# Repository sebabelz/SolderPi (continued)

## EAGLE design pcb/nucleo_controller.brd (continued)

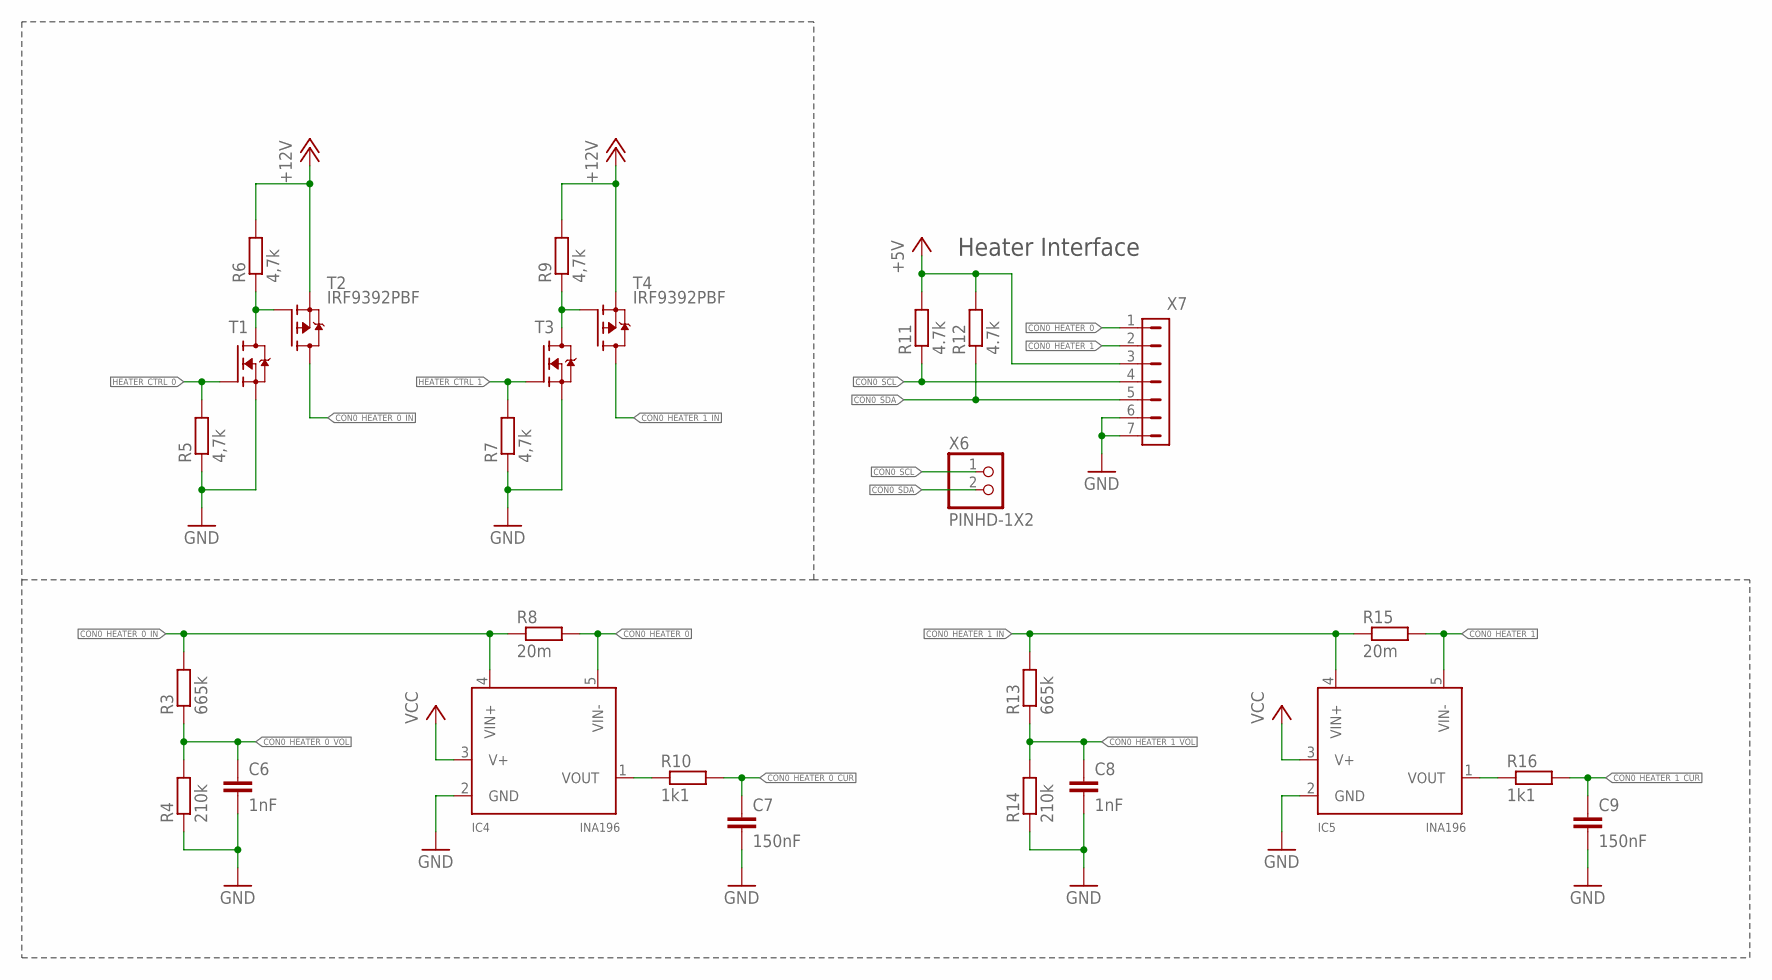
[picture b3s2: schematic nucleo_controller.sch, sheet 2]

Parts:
C6, C8: 1nF; C0603
C7, C9: 150nF; C0603
IC4, IC5: INA196; SOT23-5L
R3, R13: 665k; R0603
R4, R14: 210k; R0603
R5, R6, R7, R9: 4,7k; R0805
R8, R15: 20m; R1206
R10, R16: 1k1; R0603
R11, R12: 4.7k; R0603
T1, T3: NVR4003NT3G; SOT23
T2, T4: IRF9392PBF; SO8
X6: PINHD-1X2; 1X02
X7: NANOFIT-7

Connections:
+5V: R11.2, R12.2, X7.3; also elsewhere on the board
+12V: R6.2, R9.2, T2.1 (S), T2.2 (S), T2.3 (S), T4.1 (S), T4.2 (S), T4.3 (S); also elsewhere on the board
CON0_HEATER_0: IC4.5 (VIN-), R8.2, X7.1
CON0_HEATER_0_CUR: C7.1, R10.2; also elsewhere on the board
CON0_HEATER_0_IN: IC4.4 (VIN+), R3.2, R8.1, T2.5 (D), T2.6 (D), T2.7 (D), T2.8 (D)
CON0_HEATER_0_VOL: C6.1, R3.1, R4.2; also elsewhere on the board
CON0_HEATER_1: IC5.5 (VIN-), R15.2, X7.2
CON0_HEATER_1_CUR: C9.1, R16.2; also elsewhere on the board
CON0_HEATER_1_IN: IC5.4 (VIN+), R13.2, R15.1, T4.5 (D), T4.6 (D), T4.7 (D), T4.8 (D)
CON0_HEATER_1_VOL: C8.1, R13.1, R14.2; also elsewhere on the board
CON0_SCL: R11.1, X6.1, X7.4; also elsewhere on the board
CON0_SDA: R12.1, X6.2, X7.5; also elsewhere on the board
GND: C6.2, C7.2, C8.2, C9.2, IC4.2 (GND), IC5.2 (GND), R4.1, R5.1, R7.1, R14.1, T1.2 (S), T3.2 (S), X7.6, X7.7; also elsewhere on the board
HEATER0_AD_OUT0: IC4.1 (VOUT), R10.1
HEATER0_AD_OUT1: IC5.1 (VOUT), R16.1
HEATER0_G0: R6.1, T1.3 (D), T2.4 (G)
HEATER0_G1: R9.1, T3.3 (D), T4.4 (G)
HEATER_CTRL_0: R5.2, T1.1 (G); also elsewhere on the board
HEATER_CTRL_1: R7.2, T3.1 (G); also elsewhere on the board
VCC: IC4.3 (V+), IC5.3 (V+); also elsewhere on the board

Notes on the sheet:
Heater Interface

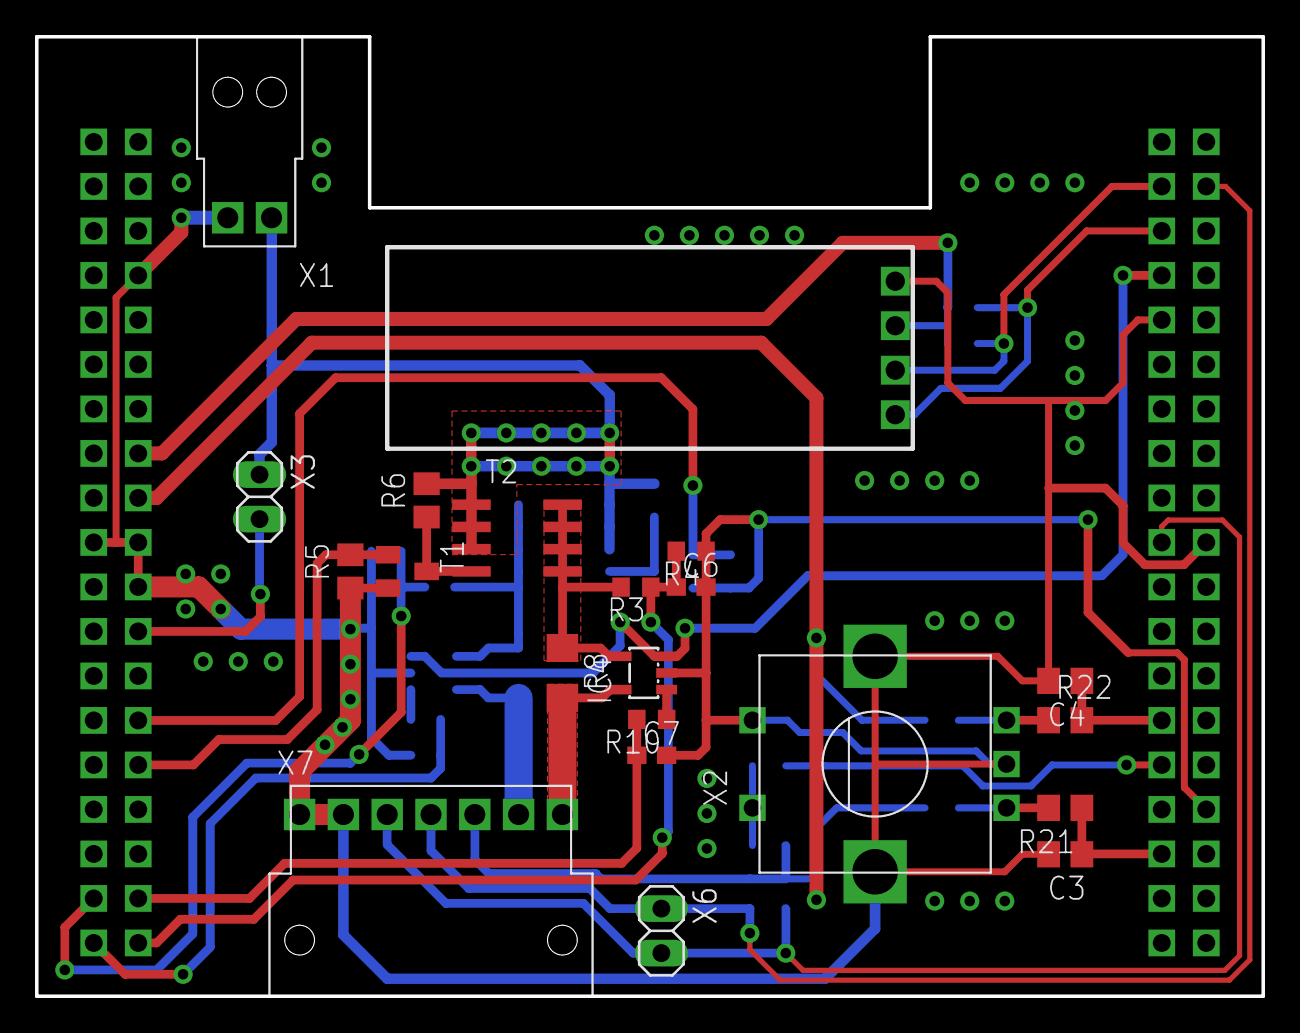
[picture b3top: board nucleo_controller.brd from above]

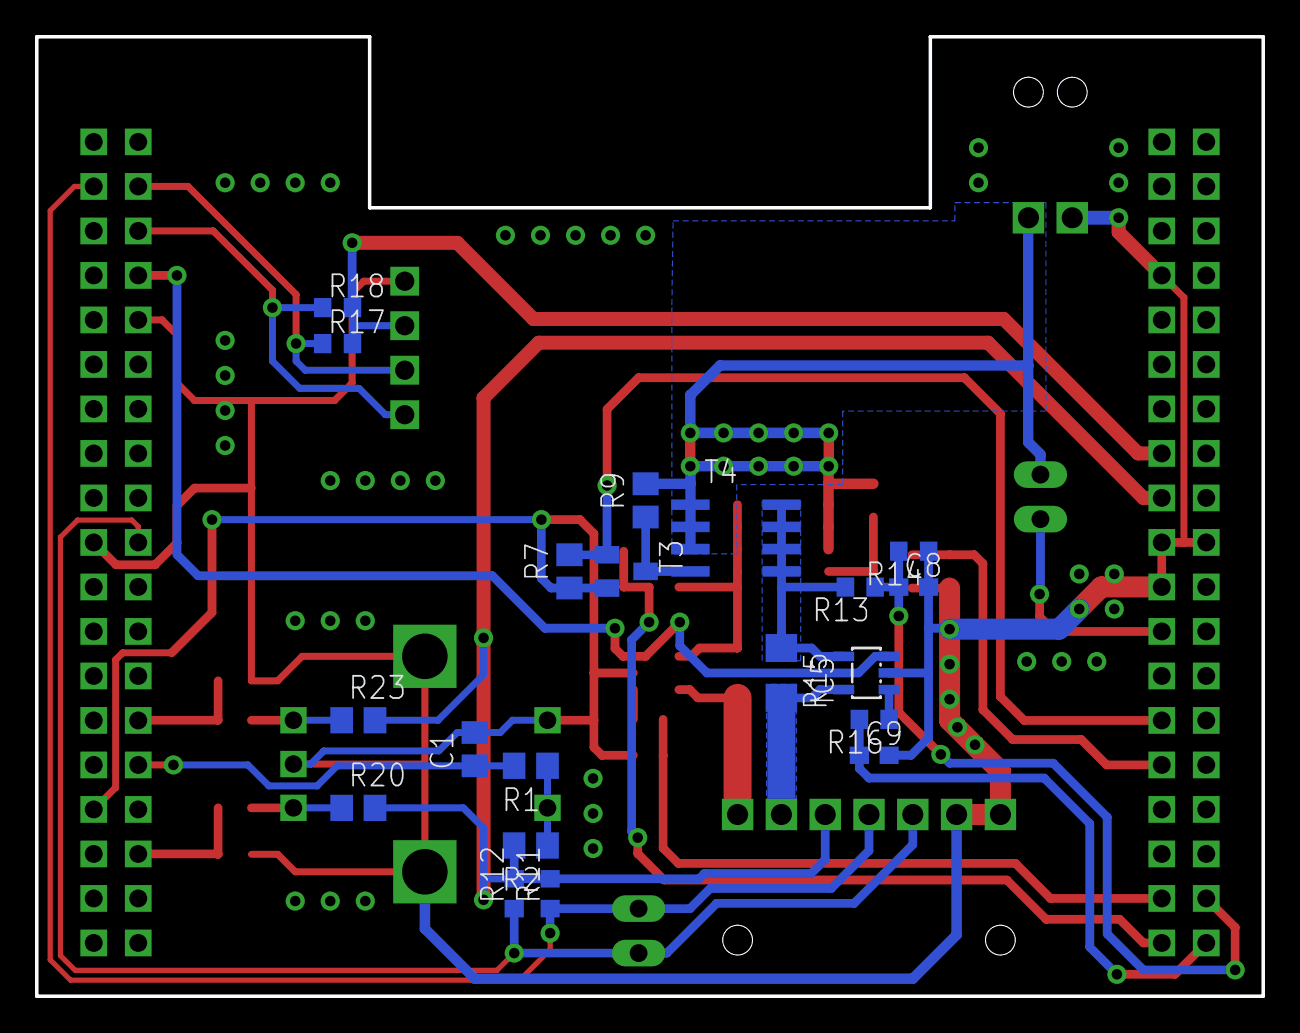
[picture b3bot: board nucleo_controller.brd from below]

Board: 2 copper layers, 70.0 x 54.8 mm, 42 parts (20 on the bottom side), 30 nets.

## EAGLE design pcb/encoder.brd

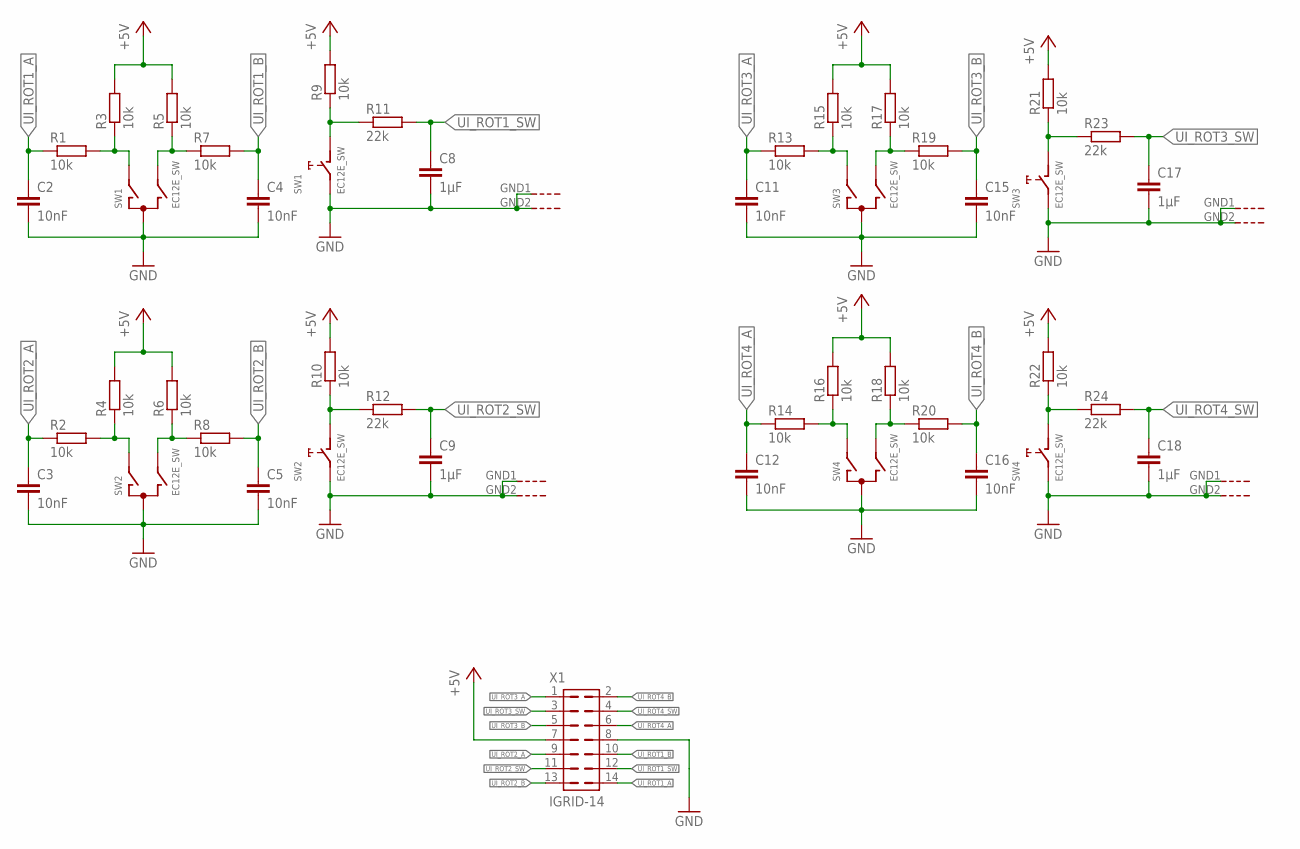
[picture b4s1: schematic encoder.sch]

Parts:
C2, C3, C4, C5, C11, C12, C15, C16: 10nF; C0805
C8, C9, C17, C18: 1µF; C0805
R1, R2, R3, R4, R5, R6, R7, R8, R9, R10, R13, R14, R15, R16, R17, R18, R19, R20, R21, R22: 10k; R0805
R11, R12, R23, R24: 22k; R0805
SW1, SW2, SW3, SW4: EC12E_SW; ALPS_EC12E_SW
X1: IGRID-14; I-GRID-14

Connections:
+5V: R3.2, R4.2, R5.2, R6.2, R9.2, R10.2, R15.2, R16.2, R17.2, R18.2, R21.2, R22.2, X1.7
GND: C2.2, C3.2, C4.2, C5.2, C8.2, C9.2, C11.2, C12.2, C15.2, C16.2, C17.2, C18.2, SW1.C, SW1.E (2), SW1.GND1 (G), SW1.GND2 (G), SW2.C, SW2.E (2), SW2.GND1 (G), SW2.GND2 (G), SW3.C, SW3.E (2), SW3.GND1 (G), SW3.GND2 (G), SW4.C, SW4.E (2), SW4.GND1 (G), SW4.GND2 (G), X1.8
UI_ROT1_A: C2.1, R1.1, X1.14
UI_ROT1_A_UNFIL: R1.2, R3.1, SW1.A
UI_ROT1_B: C4.1, R7.2, X1.10
UI_ROT1_B_UNFIL: R5.1, R7.1, SW1.B
UI_ROT1_SW: C8.1, R11.2, X1.12
UI_ROT1_SW_R: R9.1, R11.1, SW1.D (1)
UI_ROT2_A: C3.1, R2.1, X1.9
UI_ROT2_A_UNFIL: R2.2, R4.1, SW2.A
UI_ROT2_B: C5.1, R8.2, X1.13
UI_ROT2_B_UNFIL: R6.1, R8.1, SW2.B
UI_ROT2_SW: C9.1, R12.2, X1.11
UI_ROT2_SW_R: R10.1, R12.1, SW2.D (1)
UI_ROT3_A: C11.1, R13.1, X1.1
UI_ROT3_A_UNFIL: R13.2, R15.1, SW3.A
UI_ROT3_B: C15.1, R19.2, X1.5
UI_ROT3_B_UNFIL: R17.1, R19.1, SW3.B
UI_ROT3_SW: C17.1, R23.2, X1.3
UI_ROT3_SW_R: R21.1, R23.1, SW3.D (1)
UI_ROT4_A: C12.1, R14.1, X1.6
UI_ROT4_A_UNFIL: R14.2, R16.1, SW4.A
UI_ROT4_B: C16.1, R20.2, X1.2
UI_ROT4_B_UNFIL: R18.1, R20.1, SW4.B
UI_ROT4_SW: C18.1, R24.2, X1.4
UI_ROT4_SW_R: R22.1, R24.1, SW4.D (1)

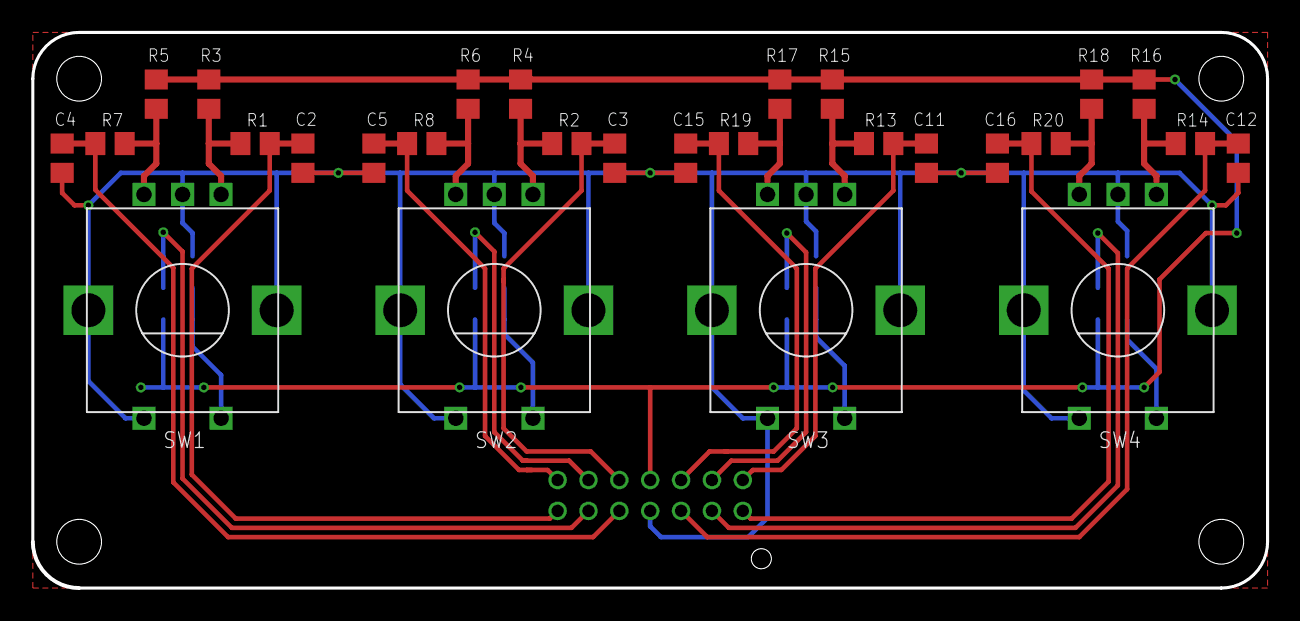
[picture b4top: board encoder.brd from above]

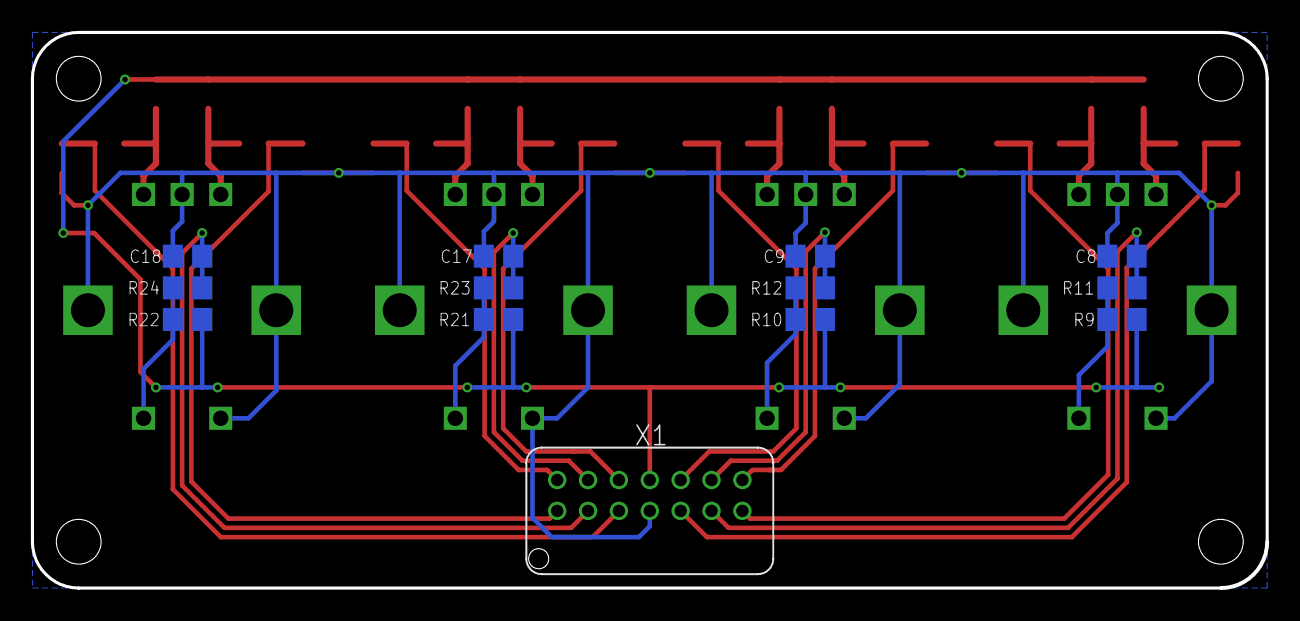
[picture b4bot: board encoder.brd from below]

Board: 2 copper layers, 80.0 x 36.0 mm, 41 parts (13 on the bottom side), 26 nets.

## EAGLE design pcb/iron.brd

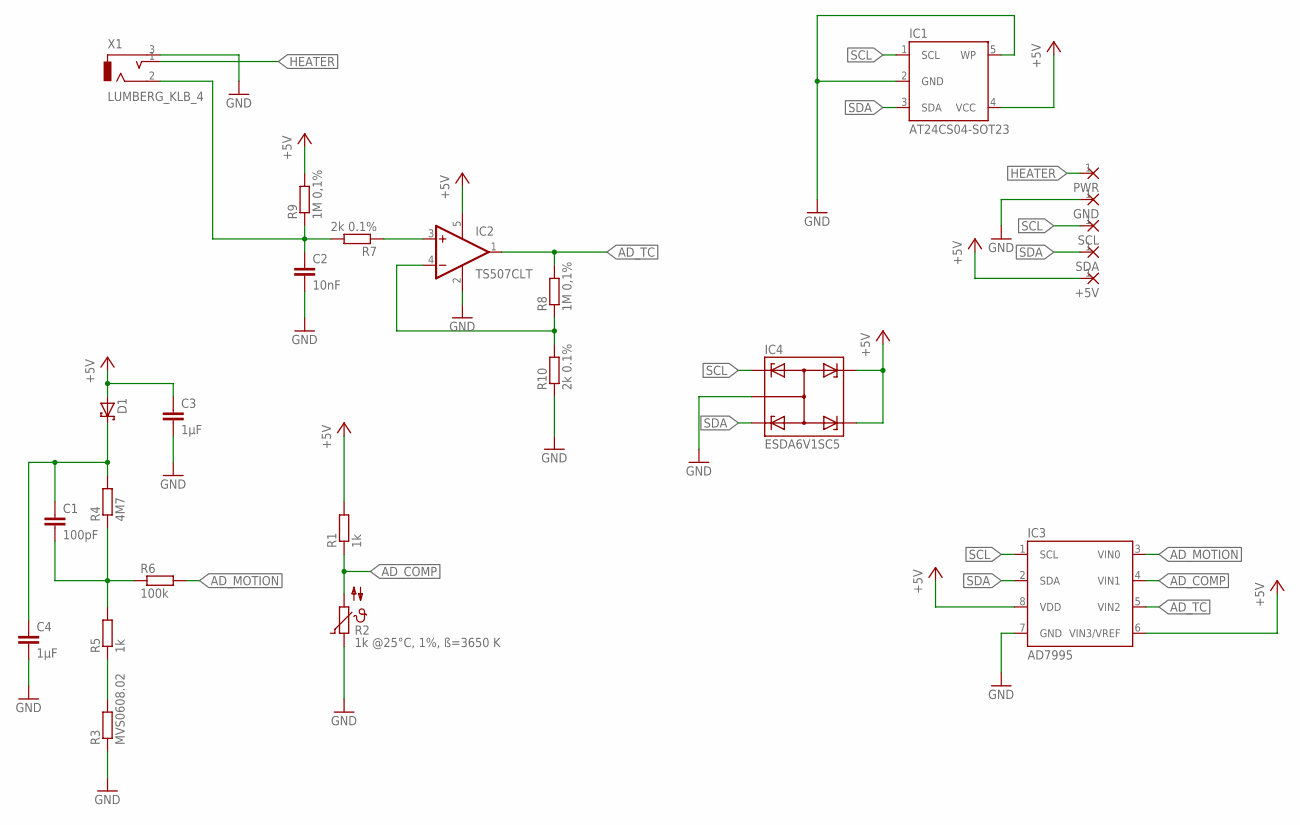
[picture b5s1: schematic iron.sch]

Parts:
+5V: 1,6/0,8
C1: 100pF; C0603
C2: 10nF; C0603
C3, C4: 1µF; C0603
D1: BAT54H; SOD123-F
GND: 1,6/0,8
IC1: AT24CS04-SOT23; SOT23-5L
IC2: TS507CLT; SOT23-5L
IC3: AD7995; SOT23-8
IC4: ESDA6V1SC5; SOT23-5L
PWR: 1,6/0,8
R1, R5: 1k; R0603
R2: 1k @25°C, 1%, ß=3650 K; R0603
R3: MVS0608.02; VIBRA-SNS
R4: 4M7; R0603
R6: 100k; R0603
R7, R10: 2k 0.1%; R0603
R8, R9: 1M 0,1%; R0603
SCL: 1,6/0,8
SDA: 1,6/0,8
X1: LUMBERG_KLB_4; 3.5_MM_AUDIO_JACK

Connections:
+5V: +5V.1, C3.1, D1.2 (A), IC1.4 (VCC), IC2.5 (V+), IC3.6 (VIN3/VREF), IC3.8 (VDD), IC4.4, IC4.5, R1.2, R9.2
AD_COMP: IC3.4 (VIN1), R1.1, R2.2
AD_MOTION: IC3.3 (VIN0), R6.2
AD_TC: IC2.1 (OUT), IC3.5 (VIN2), R8.2
FEEDBACK: IC2.4 (-IN), R8.1, R10.2
GND: C2.2, C3.2, C4.2, GND.1, IC1.2 (GND), IC1.5 (WP), IC2.2 (V-), IC3.7 (GND), IC4.2, R2.1, R3.P$1 (1), R10.1, X1.3
HEATER: PWR.1, X1.1
MOTION_DIV: R3.P$2 (2), R5.1
MOTION_FIL: C1.2, R4.1, R5.2, R6.1
unnamed: C1.1, C4.1, D1.1 (C), R4.2
SCL: IC1.1 (SCL), IC3.1 (SCL), IC4.1, SCL.1
SDA: IC1.3 (SDA), IC3.2 (SDA), IC4.3, SDA.1
THERMO_FIL: IC2.3 (+IN), R7.1
THERMO_UNFIL: C2.1, R7.2, R9.1, X1.2

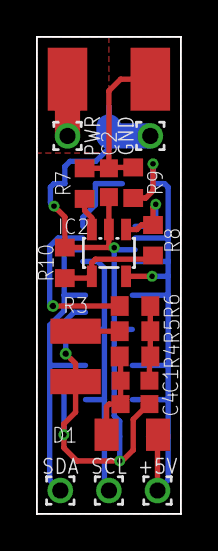
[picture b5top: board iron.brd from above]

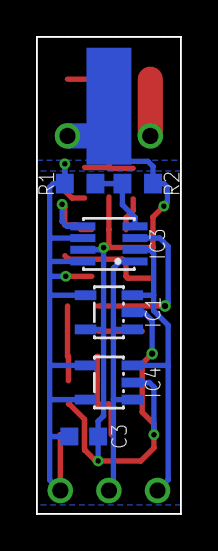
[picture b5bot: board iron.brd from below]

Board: 2 copper layers, 8.0 x 26.5 mm, 25 parts (7 on the bottom side), 14 nets.

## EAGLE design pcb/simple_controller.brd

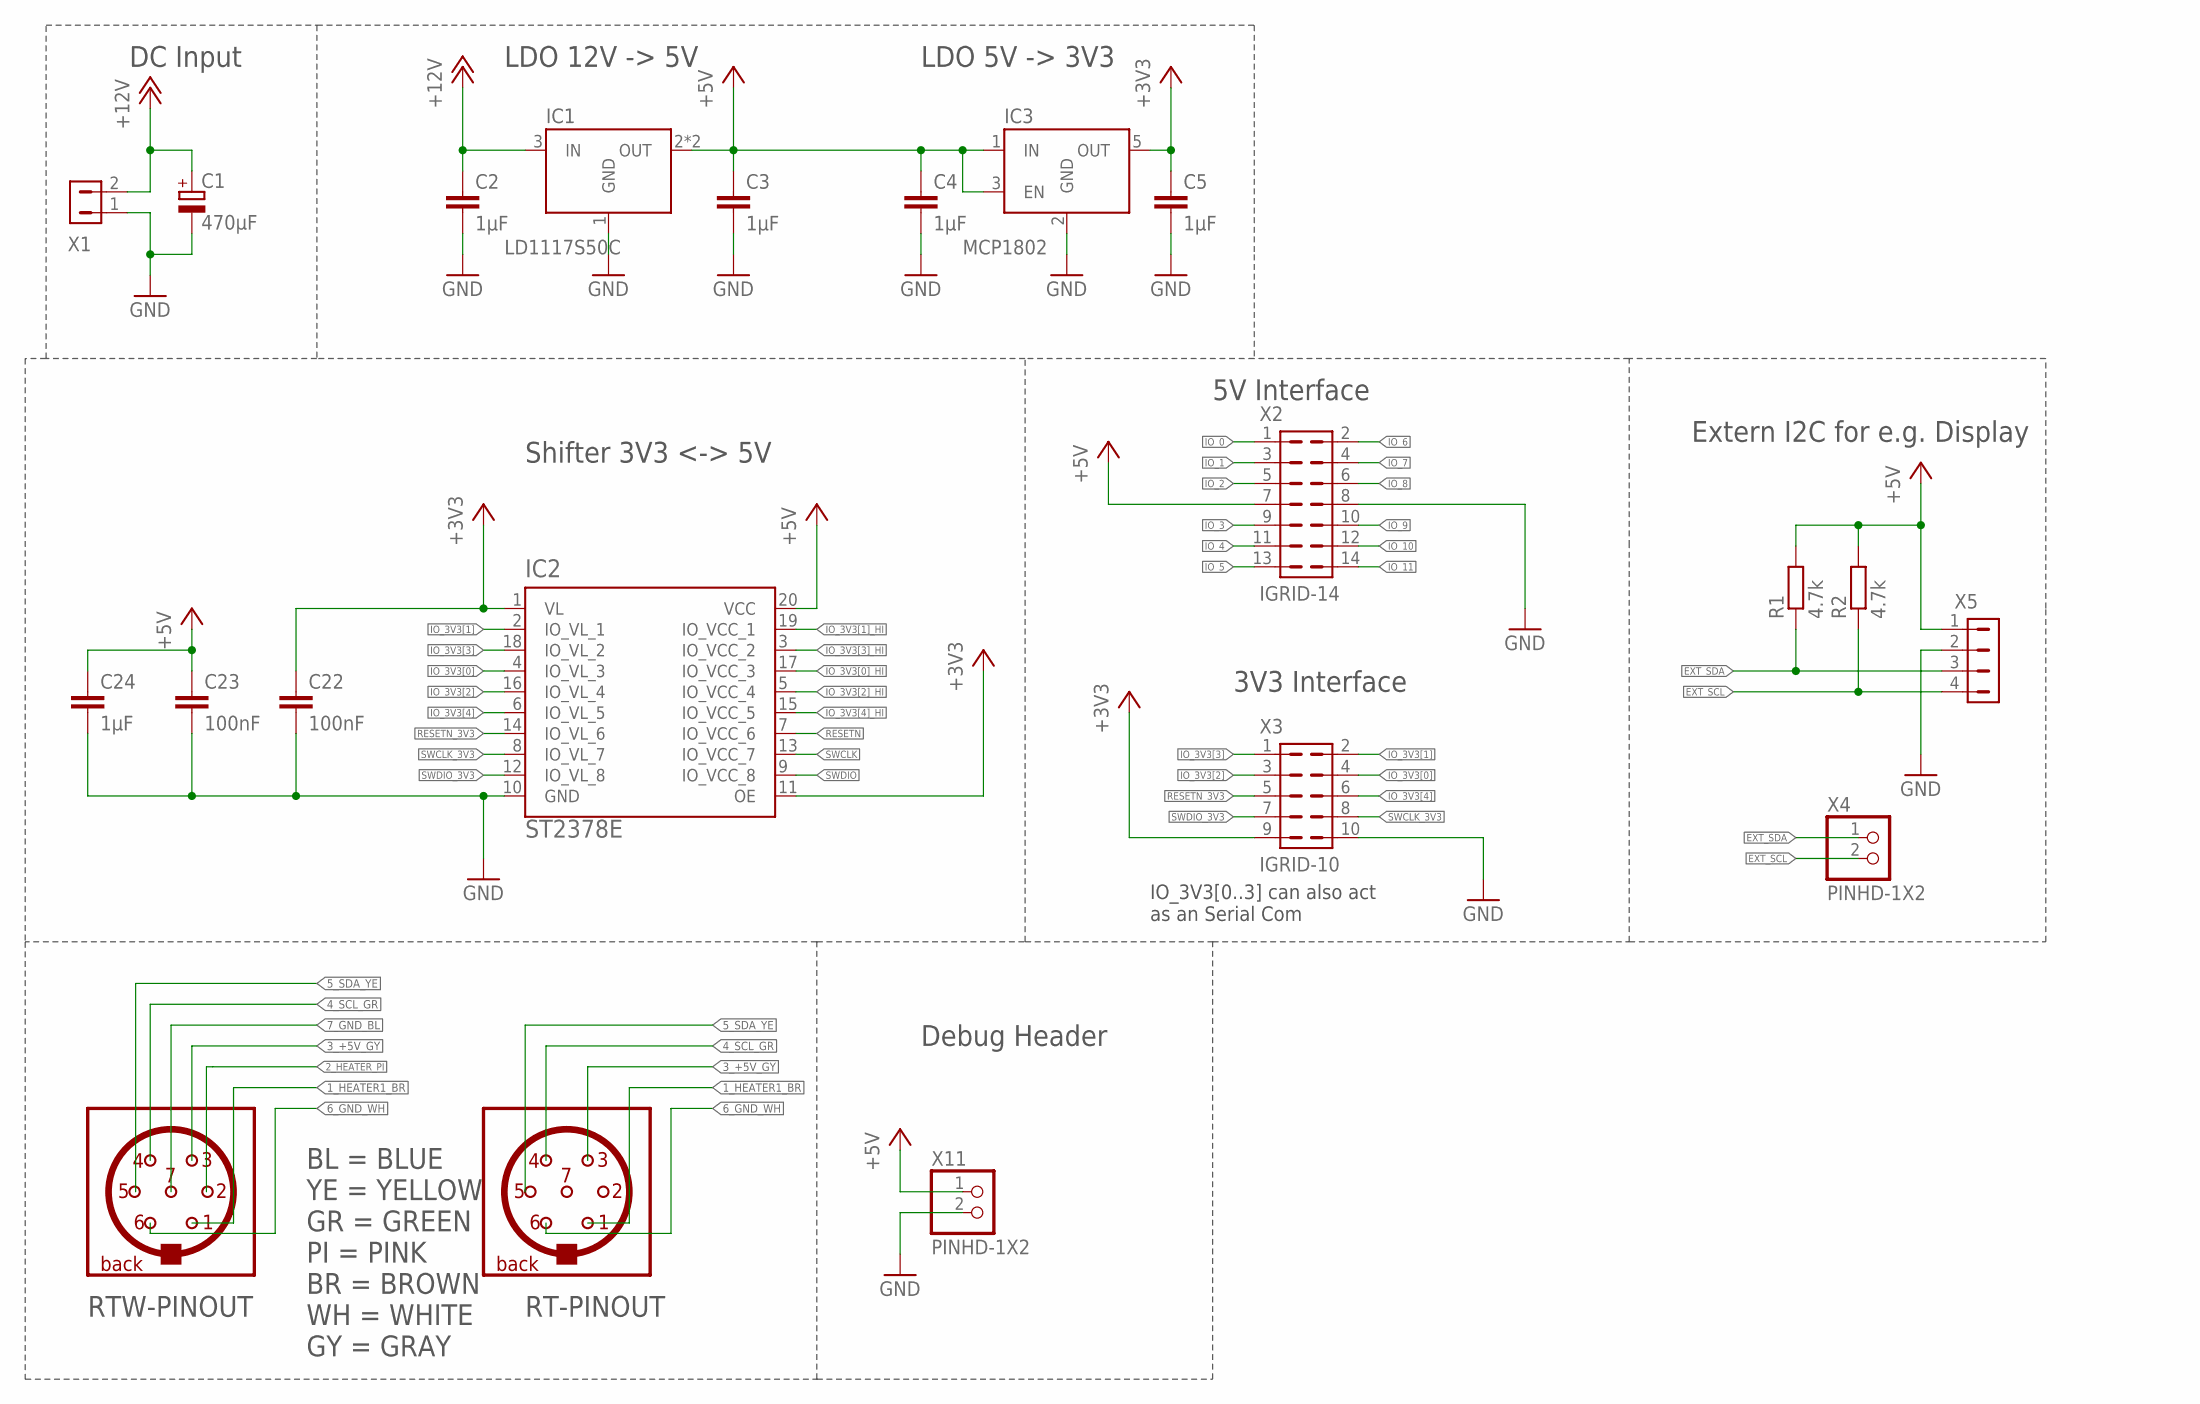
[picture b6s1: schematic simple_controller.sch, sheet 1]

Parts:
C1: 470µF; C_EEEFK-10X10
C2, C3, C4, C5: 1µF; C0805
C22, C23: 100nF; C0402
C24: 1µF; C0402
IC1: LD1117S50C; SOT223
IC2: ST2378E; TSSOP20
IC3: MCP1802; SOT23-5L
R1, R2: 4.7k; R0603
X1: NANOFIT-2; NANOFIT-2-90
X2: IGRID-14; I-GRID-14
X3: IGRID-10; I-GRID-10
X4, X11: PINHD-1X2; 1X02
X5: MICRO-LATCH-4

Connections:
+3V3: C5.1, C22.1, IC2.1 (VL), IC2.11 (OE), IC3.5 (OUT), X3.9
+5V: C3.1, C4.1, C23.1, C24.1, IC1.2 (OUT), IC1.4 (OUT), IC2.20 (VCC), IC3.1 (IN), IC3.3 (EN), R1.2, R2.2, X2.7, X5.1, X11.1; also elsewhere on the board
+12V: C1.+, C2.1, IC1.3 (IN), X1.2; also elsewhere on the board
EXT_SCL: R2.1, X4.2, X5.4; also elsewhere on the board
EXT_SDA: R1.1, X4.1, X5.3; also elsewhere on the board
GND: C1.-, C2.2, C3.2, C4.2, C5.2, C22.2, C23.2, C24.2, IC1.1 (GND), IC2.10 (GND), IC3.2 (GND), X1.1, X2.8, X3.10, X5.2, X11.2; also elsewhere on the board
IO_0: X2.1; also elsewhere on the board
IO_1: X2.3; also elsewhere on the board
IO_2: X2.5; also elsewhere on the board
IO_3: X2.9; also elsewhere on the board
IO_3V3[0]: IC2.4 (IO_VL_3), X3.4
IO_3V3[0]_HI: IC2.17 (IO_VCC_3); also elsewhere on the board
IO_3V3[1]: IC2.2 (IO_VL_1), X3.2
IO_3V3[1]_HI: IC2.19 (IO_VCC_1); also elsewhere on the board
IO_3V3[2]: IC2.16 (IO_VL_4), X3.3
IO_3V3[2]_HI: IC2.5 (IO_VCC_4); also elsewhere on the board
IO_3V3[3]: IC2.18 (IO_VL_2), X3.1
IO_3V3[3]_HI: IC2.3 (IO_VCC_2); also elsewhere on the board
IO_3V3[4]: IC2.6 (IO_VL_5), X3.6
IO_3V3[4]_HI: IC2.15 (IO_VCC_5); also elsewhere on the board
IO_4: X2.11; also elsewhere on the board
IO_5: X2.13; also elsewhere on the board
IO_6: X2.2; also elsewhere on the board
IO_7: X2.4; also elsewhere on the board
IO_8: X2.6; also elsewhere on the board
IO_9: X2.10; also elsewhere on the board
IO_10: X2.12; also elsewhere on the board
IO_11: X2.14; also elsewhere on the board
RESETN: IC2.7 (IO_VCC_6); also elsewhere on the board
RESETN_3V3: IC2.14 (IO_VL_6), X3.5
SWCLK: IC2.13 (IO_VCC_7); also elsewhere on the board
SWCLK_3V3: IC2.8 (IO_VL_7), X3.8
SWDIO: IC2.9 (IO_VCC_8); also elsewhere on the board
SWDIO_3V3: IC2.12 (IO_VL_8), X3.7

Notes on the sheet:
LDO 12V -> 5V
LDO 5V -> 3V3
3V3 Interface
Shifter 3V3 <-> 5V
Extern I2C for e.g. Display
BL = BLUE YE = YELLOW GR = GREEN PI = PINK BR = BROWN WH = WHITE GY = GRAY
RTW-PINOUT
RT-PINOUT
IO_3V3[0..3] can also act as an Serial Com
DC Input
5V Interface
Debug Header

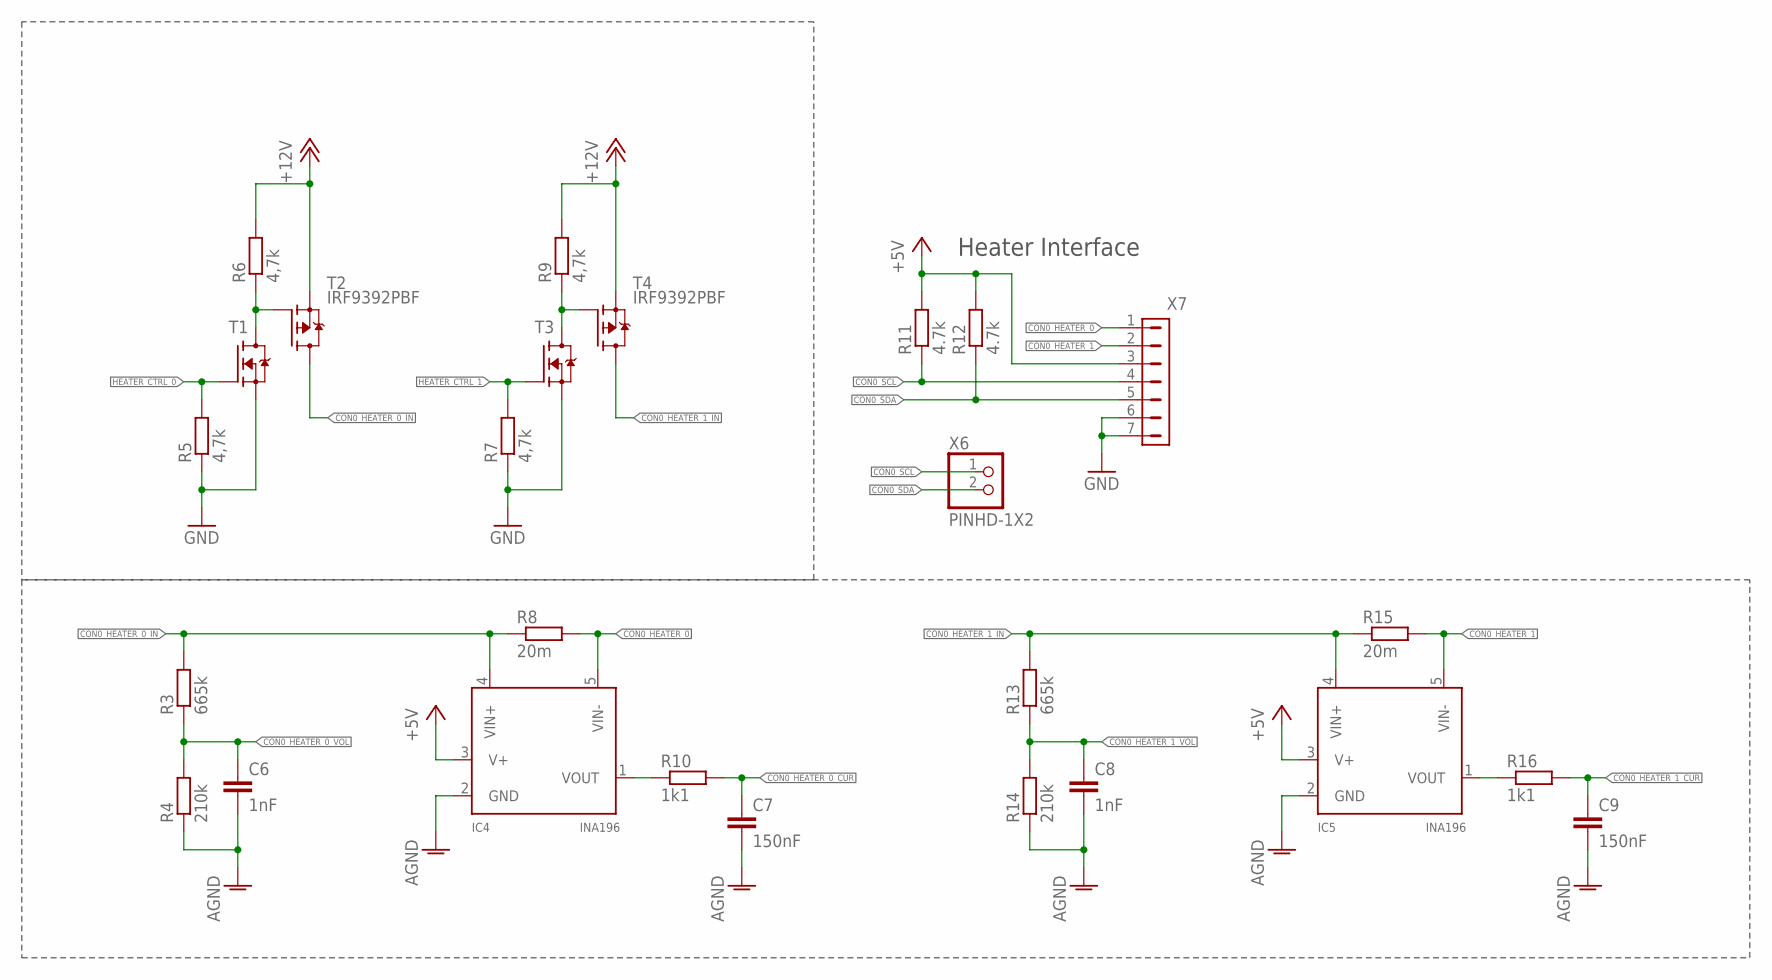
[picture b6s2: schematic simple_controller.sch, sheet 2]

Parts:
C6, C8: 1nF; C0603
C7, C9: 150nF; C0603
IC4, IC5: INA196; SOT23-5L
R3, R13: 665k; R0603
R4, R14: 210k; R0603
R5, R6, R7, R9: 4,7k; R0805
R8, R15: 20m; R1206
R10, R16: 1k1; R0603
R11, R12: 4.7k; R0603
T1, T3: NVR4003NT3G; SOT23
T2, T4: IRF9392PBF; SO8
X6: PINHD-1X2; 1X02
X7: NANOFIT-7

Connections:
+5V: IC4.3 (V+), IC5.3 (V+), R11.2, R12.2, X7.3; also elsewhere on the board
+12V: R6.2, R9.2, T2.1 (S), T2.2 (S), T2.3 (S), T4.1 (S), T4.2 (S), T4.3 (S); also elsewhere on the board
AGND: C6.2, C7.2, C8.2, C9.2, IC4.2 (GND), IC5.2 (GND), R4.1, R14.1; also elsewhere on the board
CON0_HEATER_0: IC4.5 (VIN-), R8.2, X7.1
CON0_HEATER_0_CUR: C7.1, R10.2; also elsewhere on the board
CON0_HEATER_0_IN: IC4.4 (VIN+), R3.2, R8.1, T2.5 (D), T2.6 (D), T2.7 (D), T2.8 (D)
CON0_HEATER_0_VOL: C6.1, R3.1, R4.2; also elsewhere on the board
CON0_HEATER_1: IC5.5 (VIN-), R15.2, X7.2
CON0_HEATER_1_CUR: C9.1, R16.2; also elsewhere on the board
CON0_HEATER_1_IN: IC5.4 (VIN+), R13.2, R15.1, T4.5 (D), T4.6 (D), T4.7 (D), T4.8 (D)
CON0_HEATER_1_VOL: C8.1, R13.1, R14.2; also elsewhere on the board
CON0_SCL: R11.1, X6.1, X7.4; also elsewhere on the board
CON0_SDA: R12.1, X6.2, X7.5; also elsewhere on the board
GND: R5.1, R7.1, T1.2 (S), T3.2 (S), X7.6, X7.7; also elsewhere on the board
HEATER0_AD_OUT0: IC4.1 (VOUT), R10.1
HEATER0_AD_OUT1: IC5.1 (VOUT), R16.1
HEATER0_G0: R6.1, T1.3 (D), T2.4 (G)
HEATER0_G1: R9.1, T3.3 (D), T4.4 (G)
HEATER_CTRL_0: R5.2, T1.1 (G); also elsewhere on the board
HEATER_CTRL_1: R7.2, T3.1 (G); also elsewhere on the board

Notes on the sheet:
Heater Interface
